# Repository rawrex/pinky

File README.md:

krylo is a 34 key column-staggered split keyboard running [ZMK](https://zmk.dev/)

Core ideas that motivated the project:
- (My) krylo moves to the side better than it reaches forward to the upper row.
- Single PCB symmetrical definition for both sides of the split.

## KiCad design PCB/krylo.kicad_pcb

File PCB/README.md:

# Pinky PCB

## MANUFACTURING
If you want to get the PCB made you need to upload the **Pinky_0-2_gerbers.zip** file to the website of the manufacture ([JLCPCB](https://jlcpcb.com/) for example).

- upload the ZIP
- sometimes the Gerber preview from JLCPCB can't display the PCB, even when the files are fine. In this case use this dimensions: 120.5 mm* 85.5 mm
- PCB Thickness 1.6mm
- 2 layers
- PCB Qty as much as you like. But be aware, that you need 2 PCBs for one keyboard
- PCB Color Black
- No impedance control
- Surface Finish HASL(with lead) if you want the easiest soldering experience or LeadFree HASL.
- Remove Order Number Yes

## CHECK TRACES OR PINOUT

If you only want to check the traces or see what is connected to which pin you can take a look at these graphics.

## TAKE A DEEPER LOOK OR MODIFY 

You can download the project if you need to take a deeper look or modify something. You need the Open Source software [KiCad](https://www.kicad.org/) to open it.

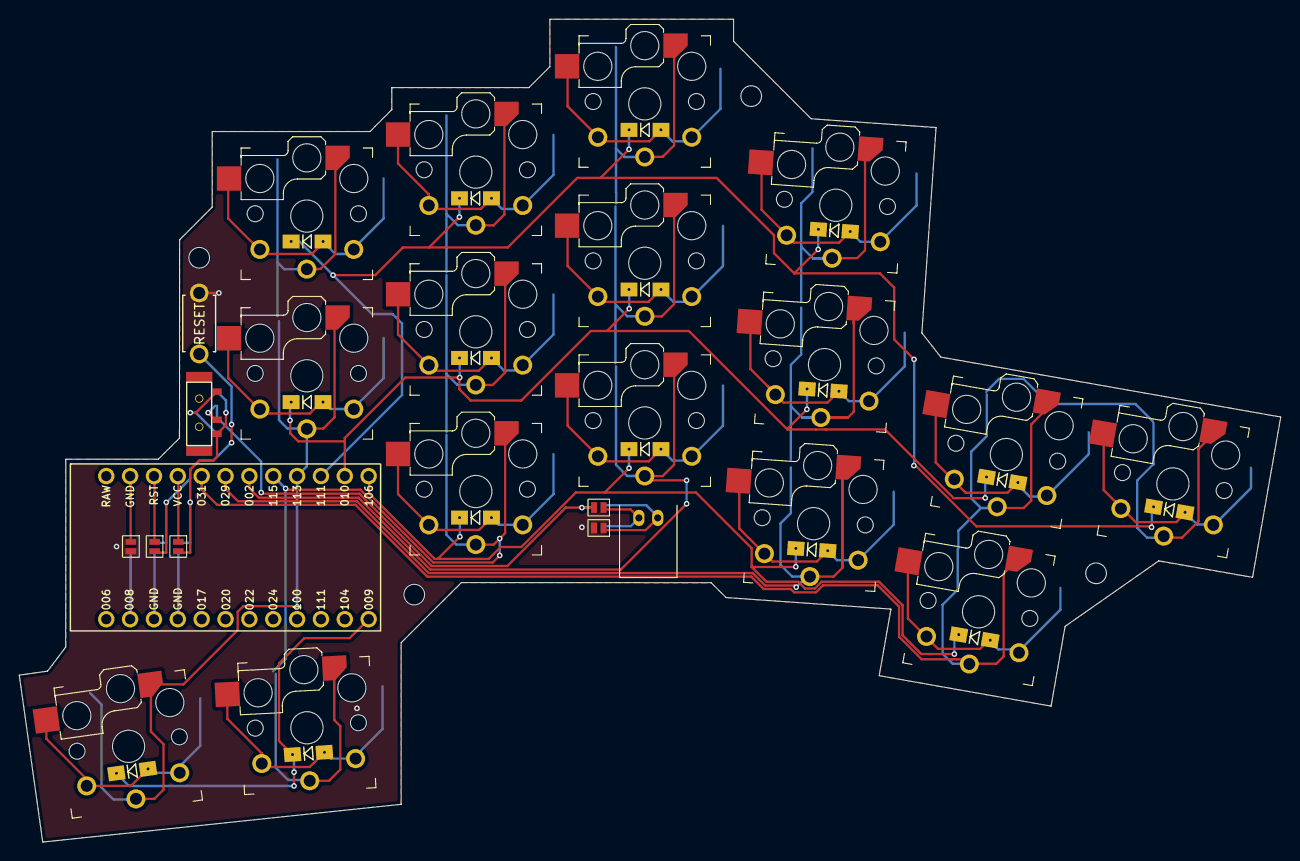
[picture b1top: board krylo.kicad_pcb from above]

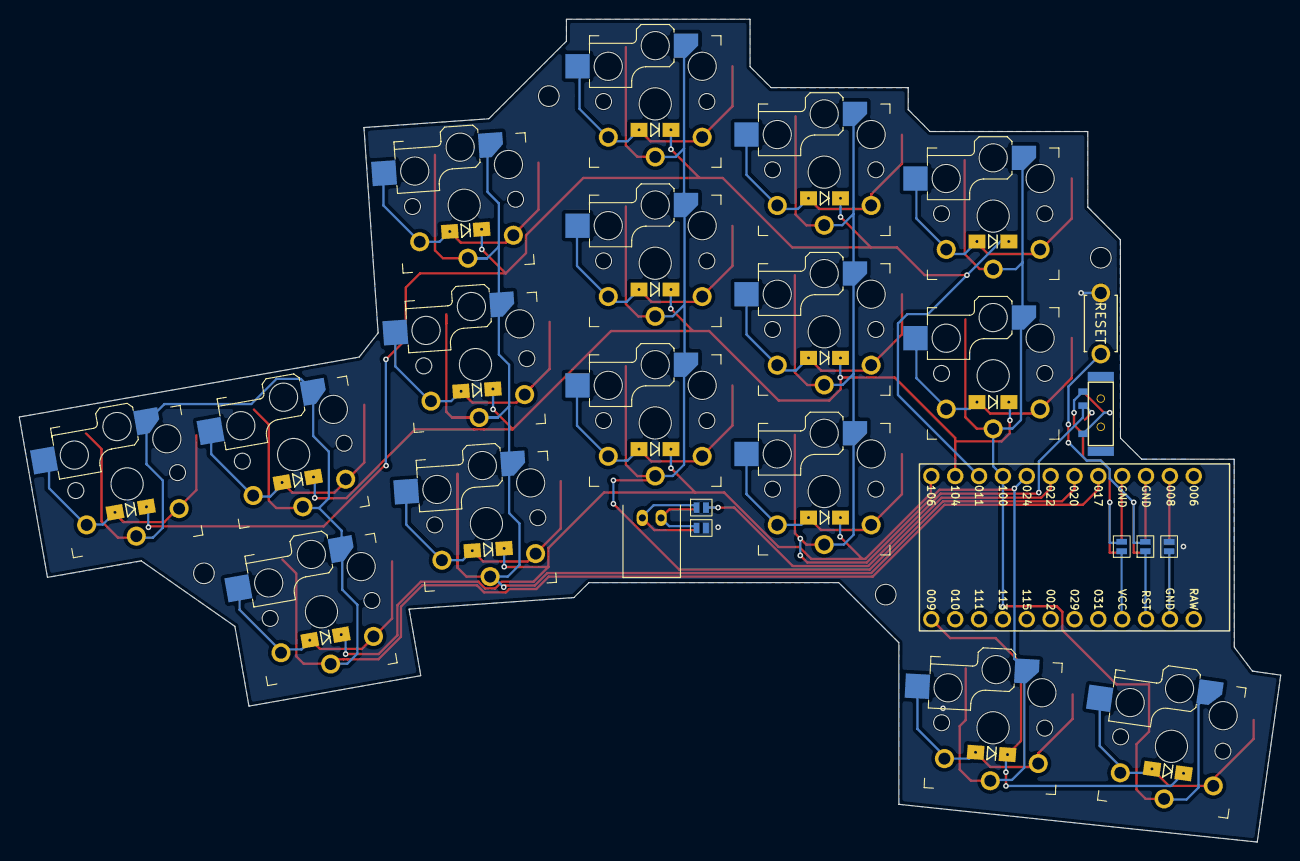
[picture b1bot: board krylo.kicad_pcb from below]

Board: 2 copper layers, 134.3 x 87.6 mm, 50 parts (6 on the bottom side), 34 nets.

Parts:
BT1: JST_PH
D1, D2, D3, D4, D5, D6, D7, D8, D9, D10, D11, D12, D13, D14, D15, D16: D_SOD123
H1, H2, H3, H4: MountingHole
JP1, JP2, JP3, JP4, JP5, JP6, JP7, JP8, JP9, JP10: Jumper
RESET1: ResetSW
SW1, SW2, SW3, SW4, SW5, SW6, SW7, SW8, SW9, SW10, SW11, SW12, SW13, SW14, SW15, SW16: Switch
SW_PWR1: MSK12C02
U1: nice_nano

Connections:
+BATT: JP9.2, JP10.2, SW_PWR1.3 (A)
+BATT_indirect: JP9.1, JP10.1, U1.4 (GND), U1.16 (EXT_VCC)
/PAD1: BT1.1 (+), JP4.1, JP5.1
/PAD2: BT1.2 (-), JP6.1, JP7.1
GND: JP1.2, JP2.2, JP4.2, JP7.2, RESET1.1
GND_indirect: JP1.1, JP2.1, U1.2 (D0/P0.08), U1.14 (GND)
unnamed: D1.2 (A), SW1.2
unnamed: D2.2 (A), SW2.2
unnamed: D3.2 (A), SW3.2
unnamed: D4.2 (A), SW4.2
unnamed: D5.2 (A), SW5.2
unnamed: D6.2 (A), SW6.2
unnamed: D7.2 (A), SW7.2
unnamed: D8.2 (A), SW8.2
unnamed: D9.2 (A), SW9.2
unnamed: D10.2 (A), SW10.2
unnamed: D11.2 (A), SW11.2
unnamed: D12.2 (A), SW12.2
unnamed: D13.2 (A), SW13.2
unnamed: D14.2 (A), SW14.2
unnamed: D15.2 (A), SW15.2
unnamed: D16.2 (A), SW16.2
unnamed: JP5.2, JP6.2, SW_PWR1.2 (B)
RESET: JP3.2, JP8.2, RESET1.2
RESET_indirect: JP3.1, JP8.1, U1.3 (GND), U1.15 (RESET)
col_A: SW1.1, SW2.1, SW3.1, U1.9 (D6/P1.00)
col_B: SW4.1, SW5.1, SW6.1, SW7.1, U1.8 (D5/P0.24)
col_C: SW8.1, SW9.1, SW10.1, U1.7 (D4/P0.22)
col_D: SW11.1, SW12.1, SW13.1, U1.6 (D3/P0.20)
col_E: SW14.1, SW15.1, SW16.1, U1.5 (D2/P0.17)
row_A: D1.1 (K), D4.1 (K), D8.1 (K), D11.1 (K), D14.1 (K), U1.10 (D7/P0.11)
row_B: D2.1 (K), D5.1 (K), D9.1 (K), D12.1 (K), D15.1 (K), U1.11 (D8/P1.04)
row_C: D6.1 (K), D10.1 (K), D13.1 (K), D16.1 (K), U1.12 (D9/P1.06)
row_D: D3.1 (K), D7.1 (K), U1.24 (D10/P0.09)

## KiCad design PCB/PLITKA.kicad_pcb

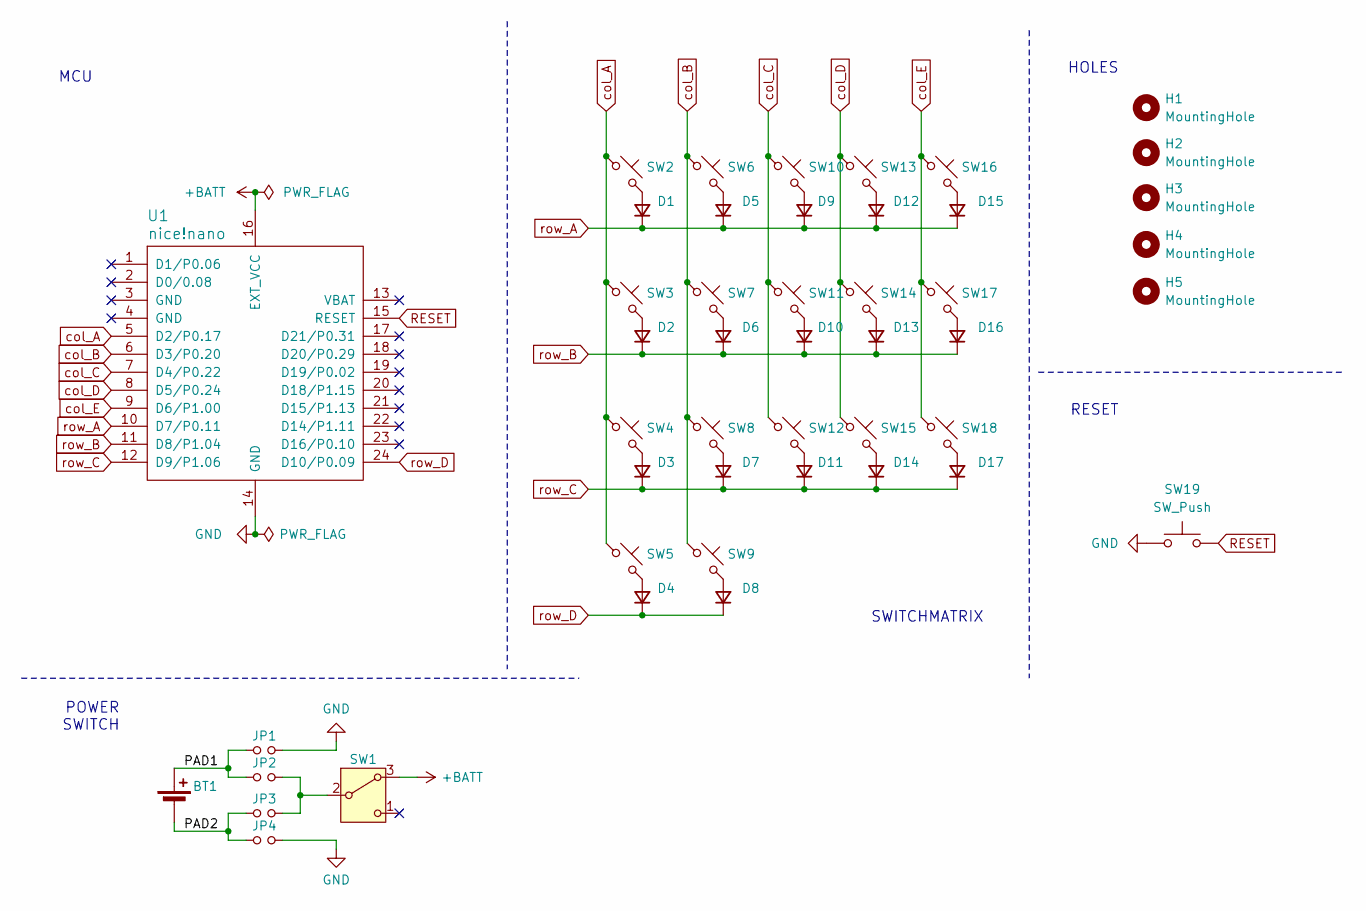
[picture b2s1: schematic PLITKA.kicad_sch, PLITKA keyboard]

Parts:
BT1: Battery_Cell
D1, D2, D3, D4, D5, D6, D7, D8, D9, D10, D11, D12, D13, D14, D15, D16, D17: D_Small
H1, H2, H3, H4, H5: MountingHole
JP1, JP2, JP3, JP4: Device_Jumper_NO_Small
SW1: SW_SPDT_321; MSK12C02_reversible
SW2, SW3, SW4, SW5, SW6, SW7, SW8, SW9, SW10, SW11, SW12, SW13, SW14, SW15, SW16, SW17, SW18: MX_SW_HS; Kailh_socket_PG1350_optional_reversible
SW19: SW_Push
U1: nice!nano; nice_nano

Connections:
+BATT: SW1.3 (A), U1.16 (EXT_VCC)
/PAD1: BT1.1 (+), JP1.1, JP2.1
/PAD2: BT1.2 (-), JP3.1, JP4.1
GND: JP1.2, JP4.2, SW19.1, U1.14 (GND)
unnamed: D1.2 (A), SW2.2
unnamed: D2.2 (A), SW3.2
unnamed: D3.2 (A), SW4.2
unnamed: D4.2 (A), SW5.2
unnamed: D5.2 (A), SW6.2
unnamed: D6.2 (A), SW7.2
unnamed: D7.2 (A), SW8.2
unnamed: D8.2 (A), SW9.2
unnamed: D9.2 (A), SW10.2
unnamed: D10.2 (A), SW11.2
unnamed: D11.2 (A), SW12.2
unnamed: D12.2 (A), SW13.2
unnamed: D13.2 (A), SW14.2
unnamed: D14.2 (A), SW15.2
unnamed: D15.2 (A), SW16.2
unnamed: D16.2 (A), SW17.2
unnamed: D17.2 (A), SW18.2
unnamed: JP2.2, JP3.2, SW1.2 (B)
RESET: SW19.2, U1.15 (RESET)
col_A: SW2.1, SW3.1, SW4.1, SW5.1, U1.5 (D2/P0.17)
col_B: SW6.1, SW7.1, SW8.1, SW9.1, U1.6 (D3/P0.20)
col_C: SW10.1, SW11.1, SW12.1, U1.7 (D4/P0.22)
col_D: SW13.1, SW14.1, SW15.1, U1.8 (D5/P0.24)
col_E: SW16.1, SW17.1, SW18.1, U1.9 (D6/P1.00)
row_A: D1.1 (K), D5.1 (K), D9.1 (K), D12.1 (K), D15.1 (K), U1.10 (D7/P0.11)
row_B: D2.1 (K), D6.1 (K), D10.1 (K), D13.1 (K), D16.1 (K), U1.11 (D8/P1.04)
row_C: D3.1 (K), D7.1 (K), D11.1 (K), D14.1 (K), D17.1 (K), U1.12 (D9/P1.06)
row_D: D4.1 (K), D8.1 (K), U1.24 (D10/P0.09)

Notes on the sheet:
SWITCHMATRIX
POWER SWITCH
HOLES
MCU
RESET

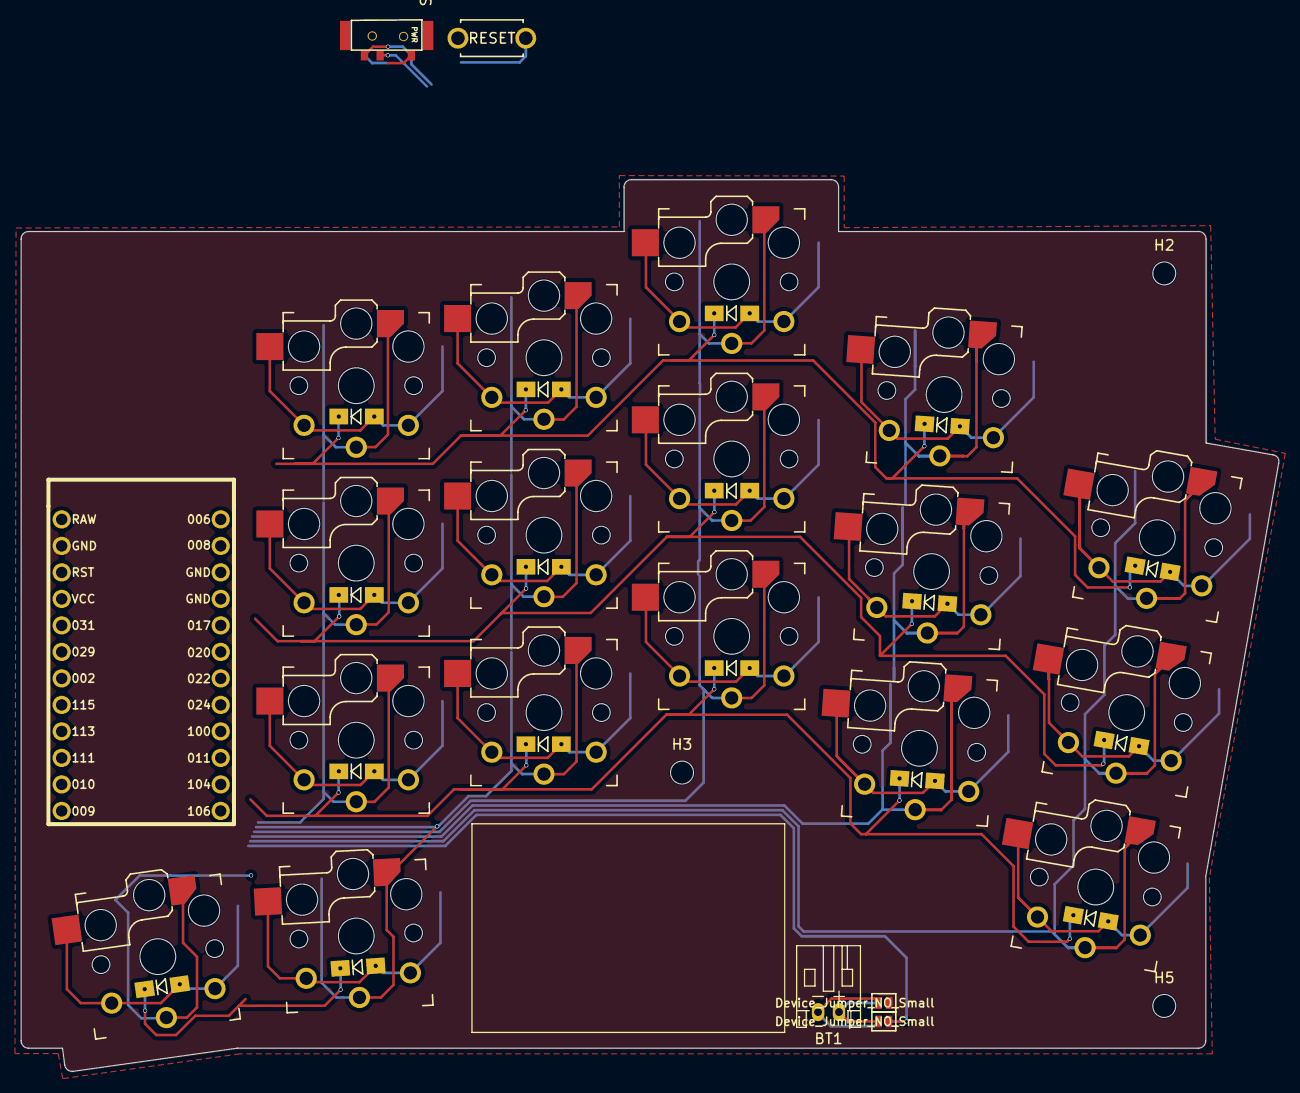
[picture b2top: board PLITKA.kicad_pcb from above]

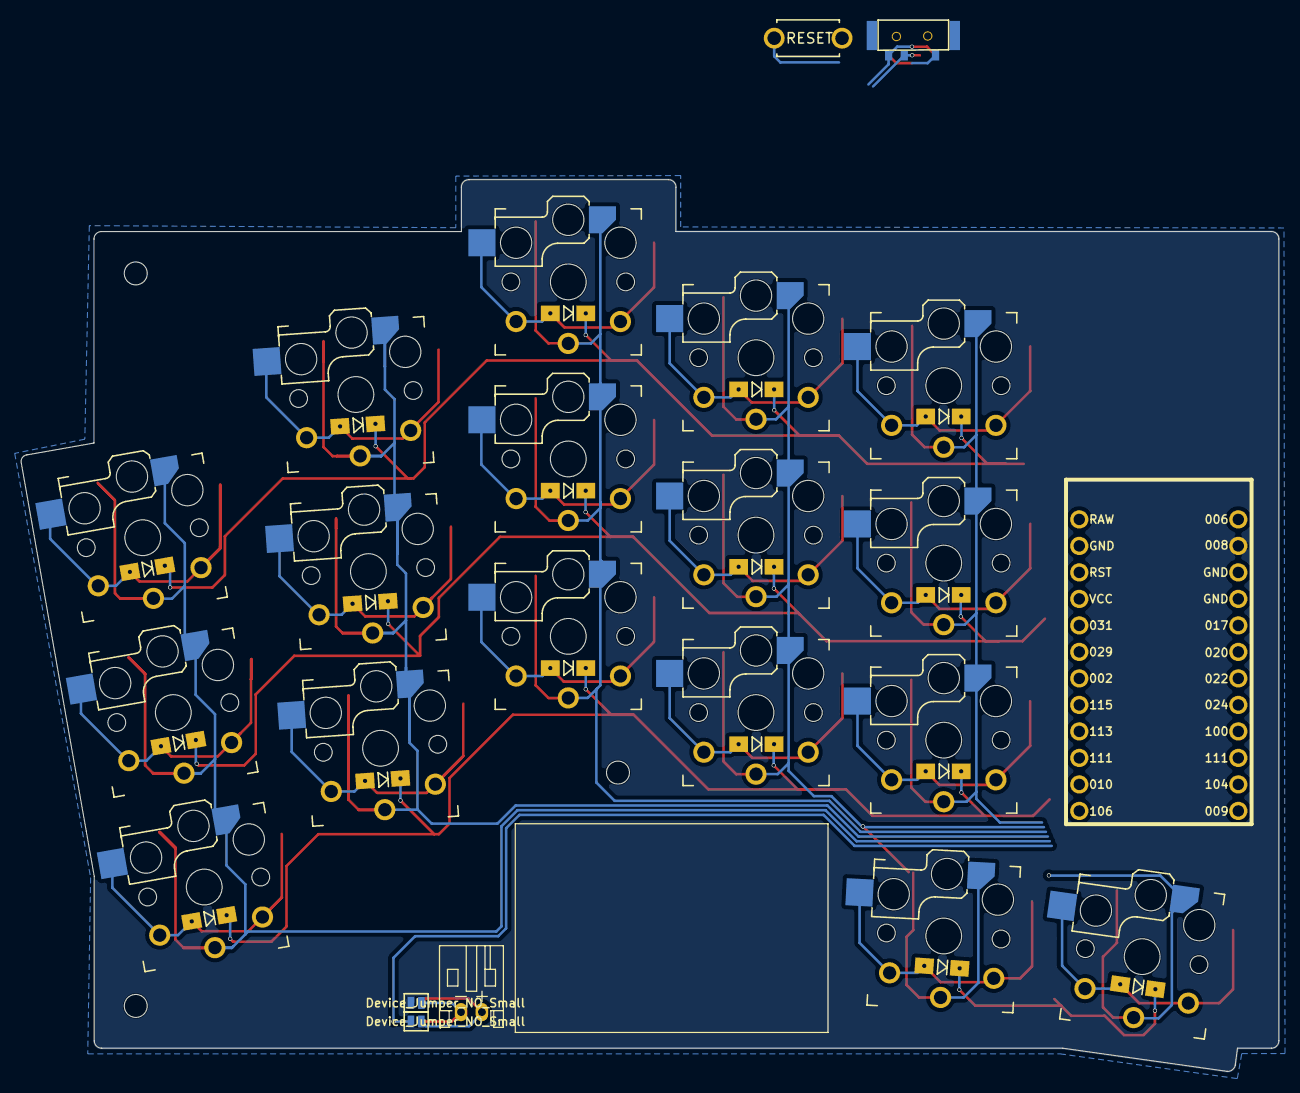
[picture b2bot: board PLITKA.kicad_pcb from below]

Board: 2 copper layers, 120.5 x 85.5 mm, 47 parts (2 on the bottom side), 32 nets.

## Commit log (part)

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2026-06-12 Cleaned up klotz references
2026-06-12 Renames
2026-06-12 Further renames
2026-06-12 KiCad versions update
2026-06-12 Removed ready-made gerbers
2026-06-12 Revision correction
2026-06-12 Encoder removal from pcb
2026-06-12 Klotz references clean up
2026-06-13 Sad logo removed
2026-06-16 Reworking the PCB to have single way to connect the MCU, added an updated nice nano footprint, updated the schematic, updated symbols
2026-06-17 Updates from schematic
2026-06-17 Nameless mechanical pad types for the powert switch mount, to avoid warnings
2026-06-17 Unused vias removal and pcb update from scheme
2026-06-17 Unused (rudimentary) footprints clean up
2026-06-17 Minimal git ignore added
2026-06-17 Orphan via removal
2026-06-17 Removed the mechanical type from the mount pads of a footprint, to avoid DRC errors
2026-06-17 Update from footprints and scheme
2026-06-17 Fabs update
2026-06-17 Pulled the fabs update
2026-06-17 Rudimentary silkscreen clean up
2026-06-18 ERC warning resolution, added the second pole-part for the double sided power switch
2026-06-18 Fix: replace SW1 DPDT symbol with SPDT to match the footprint
2026-06-18 Keyboard renamed to Pinky, to reflect the idea in the name
2026-06-18 Files clean up
2026-06-18 Removed the rudimentary docs
2026-06-18 Metadata corrections
2026-06-18 Agents file revision correction
2026-06-19 Metadata clean up
2026-06-19 Update from scheme
2026-06-19 More rudimentary symbols clean up
2026-06-19 Further symbols sync and clean up
2026-06-19 Symbol to footprint mapping
2026-06-19 Updates pull
2026-06-19 Solder mask min width rule
2026-06-20 Rudiments and paths clean up
2026-06-20 Placeholder clean up
2026-06-20 DRC vias sizing conformance
2026-06-20 Cooper refill
2026-06-21 Pcb updates pull
2026-06-22 One sided, simple jumper footprint
2026-06-22 Custom symbol definitions to avoid resetting the symbol-to-footprint mapping
2026-06-22 Names update
2026-06-22 Filters added
2026-06-22 Orphaned symbols removal
2026-06-22 Agents file update
2026-06-22 Fixed another count
2026-06-22 Further explicit Pinky library symbols to aid the mapping to the proper footprints
2026-06-22 Cache file ignore
2026-06-22 Pin name typo fix
2026-06-23 Footprint is facing proper side now
2026-06-23 Update from symbols lib
2026-06-24 Added a "decoder" of the currently active side for the power switch and cleaned up a clutter net
2026-06-26 Model rename
2026-06-26 MCU 3D model added to footprint
2026-06-26 Reset button 3D model added to the footprint
2026-06-26 Updated scheme to use two rows index finger outer column
2026-06-26 Default track width edit
2026-06-26 Shaping up the layout of the footprints
2026-06-26 Footprint updates pull
2026-06-29 Routes clean up
2026-06-29 An outline of the cuts added
2026-06-29 Footprints and scheme update
2026-06-29 Edge cuts base work done
2026-06-30 Silkscreen clipping fix
2026-06-30 Jumper footprint edit, silkscreen line is finer. Duplicated components cleaned up
2026-06-30 Revert "Silkscreen clipping fix"
    This reverts commit 03fc5d43fa8f4d5ad36e33bb0567be6cc4ce0cce.
2026-06-30 GND cooper fill added and configured
2026-06-30 Aggressive fill zone islands removal (all)
2026-06-30 Jumper courtyard added
2026-06-30 Reannotated
2026-06-30 Agents update
2026-06-30 Added ki_kb fliters to the symbols
2026-06-30 Added a note on the peculiarity of the diode connection
